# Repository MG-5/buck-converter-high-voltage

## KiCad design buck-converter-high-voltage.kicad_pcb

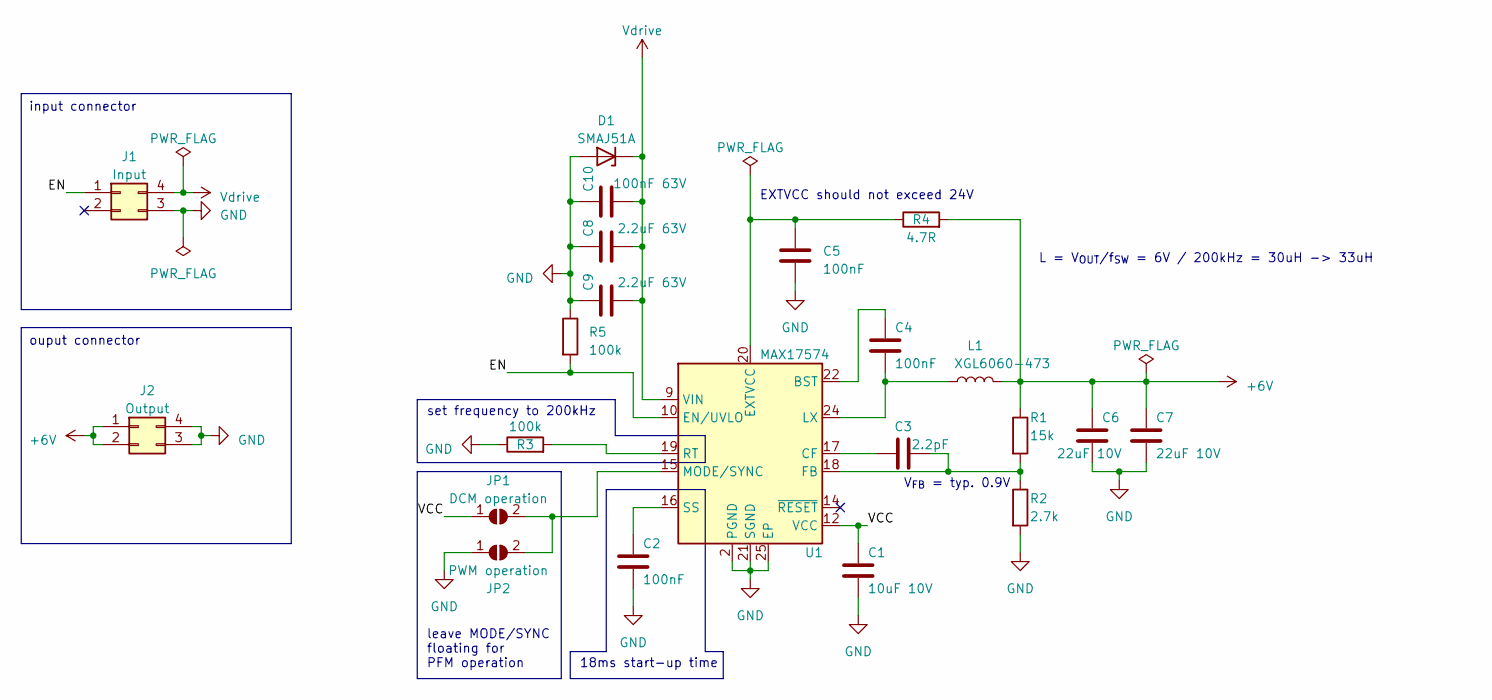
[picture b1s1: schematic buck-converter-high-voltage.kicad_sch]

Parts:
C1: 10uF 10V; C_0603_1608Metric
C2, C4, C5: 100nF; C_0603_1608Metric
C3: 2.2pF; C_0603_1608Metric
C6, C7: 22uF 10V; C_0805_2012Metric
C8, C9: 2.2uF 63V; C_0603_1608Metric
C10: 100nF 63V; C_0603_1608Metric
D1: SMAJ51A; D_SMA
J1: Input; PinHeader_2x02_P2.54mm_Vertical
J2: Output; PinHeader_2x02_P2.54mm_Horizontal
JP1: DCM operation; SolderJumper-Open_0603
JP2: PWM operation; SolderJumper-Open_0603
L1: XGL6060-473; L_Coilcraft_XAL6060-XXX
R1: 15k; R_0603_1608Metric
R2: 2.7k; R_0603_1608Metric
R3, R5: 100k; R_0603_1608Metric
R4: 4.7R; R_0603_1608Metric
U1: MAX17574; QFN-24-1EP_4x5mm_P0.5mm_EP2.65x3.65mm

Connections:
+6V: C6.2, C7.2, J2.1, J2.2, L1.2, R1.1, R4.2
/EN: J1.1, R5.2, U1.10 (EN/UVLO)
/VCC: C1.1, JP1.1 (A), U1.12 (VCC)
GND: C1.2, C2.2, C5.1, C6.1, C7.1, C8.2, C9.2, C10.2, D1.2 (A), J1.3, J2.3, J2.4, JP2.1 (A), R2.2, R3.1, R5.1, U1.2 (PGND), U1.3 (PGND), U1.11 (PGND), U1.21 (SGND), U1.25 (EP)
unnamed: C5.2, R4.1, U1.20 (EXTVCC)
unnamed: C4.1, L1.1, U1.1 (LX), U1.23 (LX), U1.24 (LX)
unnamed: JP1.2 (B), JP2.2 (B), U1.15 (MODE/SYNC)
unnamed: C4.2, U1.22 (BST)
unnamed: C3.1, U1.17 (CF)
unnamed: C3.2, R1.2, R2.1, U1.18 (FB)
unnamed: R3.2, U1.19 (RT)
unnamed: C2.1, U1.16 (SS)
Vdrive: C8.1, C9.1, C10.1, D1.1 (K), J1.4, U1.5 (VIN), U1.6 (VIN), U1.7 (VIN), U1.9 (VIN)

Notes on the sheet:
input connector
ouput connector
L = V_{OUT}/f_{SW} = 6V / 200kHz = 30uH -> 33uH
leave MODE/SYNC floating for PFM operation
set frequency to 200kHz
EXTVCC should not exceed 24V
18ms start-up time
V_{FB} = typ. 0.9V

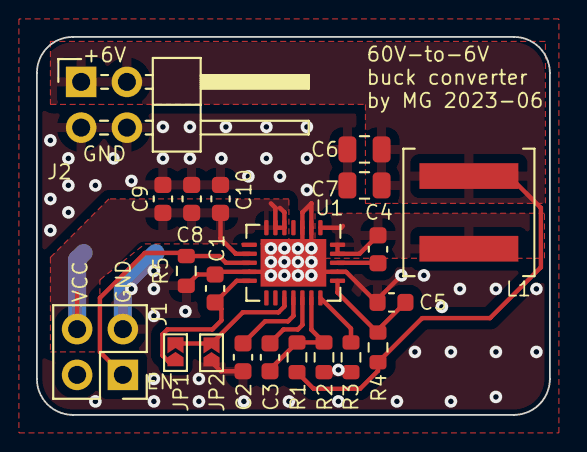
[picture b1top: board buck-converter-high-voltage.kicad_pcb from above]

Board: 2 copper layers, 28.5 x 21.0 mm, 22 parts (1 on the bottom side), 13 nets.

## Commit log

2023-06-14 Finished schematic
2023-06-14 Finished PCB
2023-06-20 Change inductor value to 47µH
